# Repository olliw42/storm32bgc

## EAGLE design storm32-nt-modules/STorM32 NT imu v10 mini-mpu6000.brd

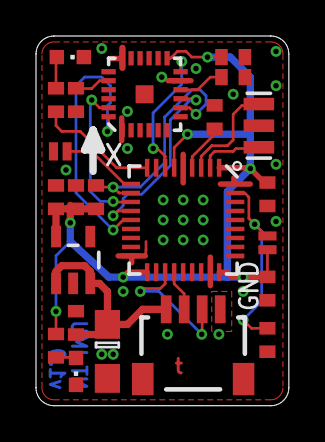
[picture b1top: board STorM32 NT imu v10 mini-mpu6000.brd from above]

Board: 2 copper layers, 14.0 x 20.5 mm, 23 parts (0 on the bottom side), 20 nets.

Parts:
C1: 10u/6.3V; SMC_A
C2, C3, C6, C8, C9, C10, C11: 100n; C0402
C5: 2.2n; C0402
C7: 1u; C0402
IC1: MPU6000; QFN-24
IC2: SOT23-5
LED1: red; CHIPLED_0603
LED2: green; CHIPLED_0603
NTX: NTX; SM04B-SRSS-TB
R1: 4.7k; R0402
R5, R7: 10k; R0402
R6: 2.2k; R0402
SJ2: BOOT0; SJ_2S-NO
SJ3: IMU-ID; SJ_2S-NO
U1: STM32F10XTXU6; VFQFPN36
Y1: RESONATORSMD; RESONATOR-SMD

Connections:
3.3V: C3.1, C7.1, C9.1, C10.1, C11.1, IC1.13, IC2.5, R1.1, R5.2, SJ2.1, U1.1, U1.6, U1.19, U1.27
5V: C1.+, C2.1, IC2.1, IC2.3, NTX.1
CS: IC1.8, R5.1, U1.11
GND: C1.-, C2.2, C3.2, C5.2, C6.2, C7.2, C8.2, C9.2, C10.2, C11.2, IC1.1, IC1.11, IC1.18, IC2.2, LED1.C, LED2.C, NTX.4, R7.1, SJ3.1, U1.5, U1.17, U1.18, U1.26, U1.36, Y1.2
INT: IC1.12, U1.7
LED: R6.1, U1.9
unnamed: C8.1, U1.4
unnamed: LED2.A, R6.2
unnamed: R7.2, SJ2.2, U1.35
unnamed: U1.2, Y1.1
unnamed: U1.3, Y1.3
unnamed: LED1.A, R1.2
unnamed: C6.1, IC1.10
unnamed: C5.1, IC1.20
RX: NTX.2, U1.22
RX2: SJ3.2, U1.10
SCL: IC1.23, U1.12
SDA: IC1.24, U1.14
SDO: IC1.9, U1.13
TX: NTX.3, U1.21

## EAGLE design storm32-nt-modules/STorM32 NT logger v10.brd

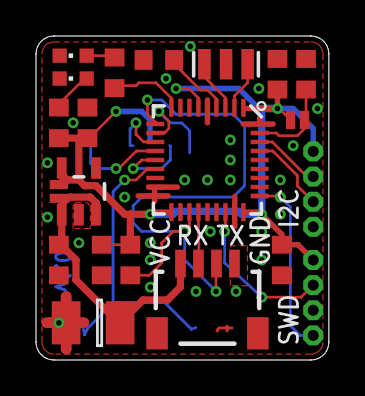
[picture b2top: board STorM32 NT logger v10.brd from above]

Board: 2 copper layers, 16.3 x 18.0 mm, 22 parts (1 on the bottom side), 21 nets.

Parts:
C1: 10u/6.3V; SMC_B
C2, C8, C9, C10, C11: 100n; C0603
C7: 1u; C0603
IC2: SOT23-5
JP1, JP2: SWD; 4X1_1P27_OCT_BILEX
LED1: red; CHIPLED_0603
LED2: green; CHIPLED_0603
NTX: NTX; SM04B-SRSS-TB
R1: 4.7k; R0603
R3: 47k; R0603
R6: 2.2k; R0603
R7: 10k; R0603
SJ1: POWER; SJ_2S-NO
SJ2: BOOT0; SJ_2S-NO
U1: STM32F10XTXU6; VFQFPN36
U$1: MICROSD
Y1: RESONATORSMD; RESONATOR-SMD

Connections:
3.3V: C7.1, C9.1, C10.1, C11.1, IC2.5, JP1.1, JP2.1, R1.1, R3.2, SJ1.2, SJ2.1, U1.1, U1.6, U1.19, U1.27, U$1.4
5V: C1.+, C2.1, IC2.1, IC2.3, NTX.1, SJ1.1
CD1: U1.15, U$1.CD1, U$1.CD2
CS: U1.11, U$1.2
GND: C1.-, C2.2, C7.2, C8.2, C9.2, C10.2, C11.2, IC2.2, JP1.4, JP2.3, LED1.C, LED2.C, NTX.4, R7.1, U1.5, U1.17, U1.18, U1.26, U1.36, U$1.6, U$1.MT1, U$1.MT2, Y1.2
LED: R6.1, U1.9
unnamed: C8.1, U1.4
unnamed: LED2.A, R6.2
unnamed: R7.2, SJ2.2, U1.35
unnamed: U1.2, Y1.1
unnamed: U1.3, Y1.3
unnamed: LED1.A, R1.2
RX: NTX.2, U1.22
SCK: U1.12, U$1.5
SCL: JP1.3, U1.33
SDA: JP1.2, U1.34
SDI: U1.14, U$1.3
SDO: U1.13, U$1.7
SWCLK: JP2.4, U1.28
SWDIO: JP2.2, U1.25
TX: NTX.3, R3.1, U1.10, U1.21

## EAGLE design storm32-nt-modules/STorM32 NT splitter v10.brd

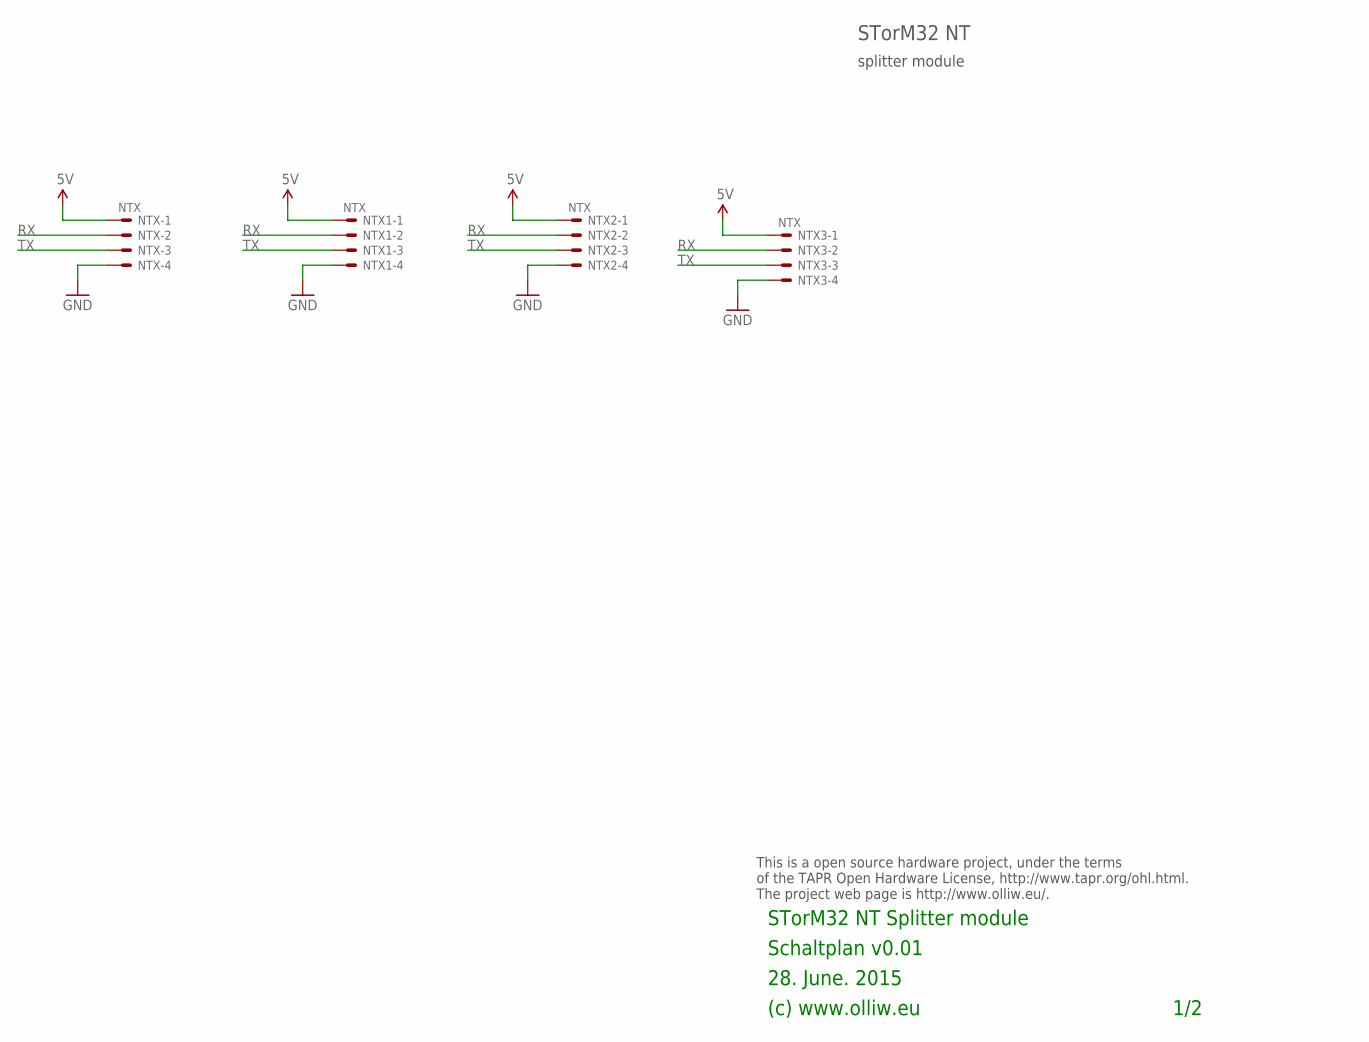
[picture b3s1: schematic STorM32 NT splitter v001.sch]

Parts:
NTX, NTX1, NTX2, NTX3: NTX; SM04B-SRSS-TB

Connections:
5V: NTX.1, NTX1.1, NTX2.1, NTX3.1
GND: NTX.4, NTX1.4, NTX2.4, NTX3.4
RX: NTX.2, NTX1.2, NTX2.2, NTX3.2
TX: NTX.3, NTX1.3, NTX2.3, NTX3.3

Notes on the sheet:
28. June. 2015
(c) www.olliw.eu
STorM32 NT Splitter module
Schaltplan v0.01
This is a open source hardware project, under the terms of the TAPR Open Hardware License, http://www.tapr.org/ohl.html. The project web page is http://www.olliw.eu/.
1/2
splitter module
STorM32 NT

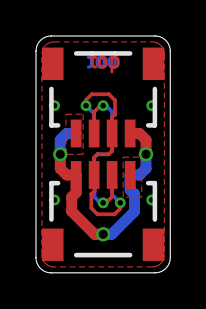
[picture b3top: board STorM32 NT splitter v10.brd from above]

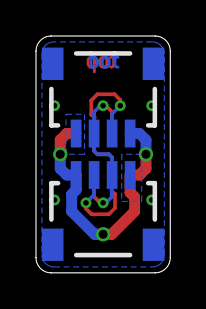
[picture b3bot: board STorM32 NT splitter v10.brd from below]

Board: 2 copper layers, 7.5 x 13.2 mm, 4 parts (2 on the bottom side), 4 nets.

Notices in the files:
parts and their libraries:
Licensing: CC v3.0 Share-Alike You are welcome to use this library for commercial purposes.
